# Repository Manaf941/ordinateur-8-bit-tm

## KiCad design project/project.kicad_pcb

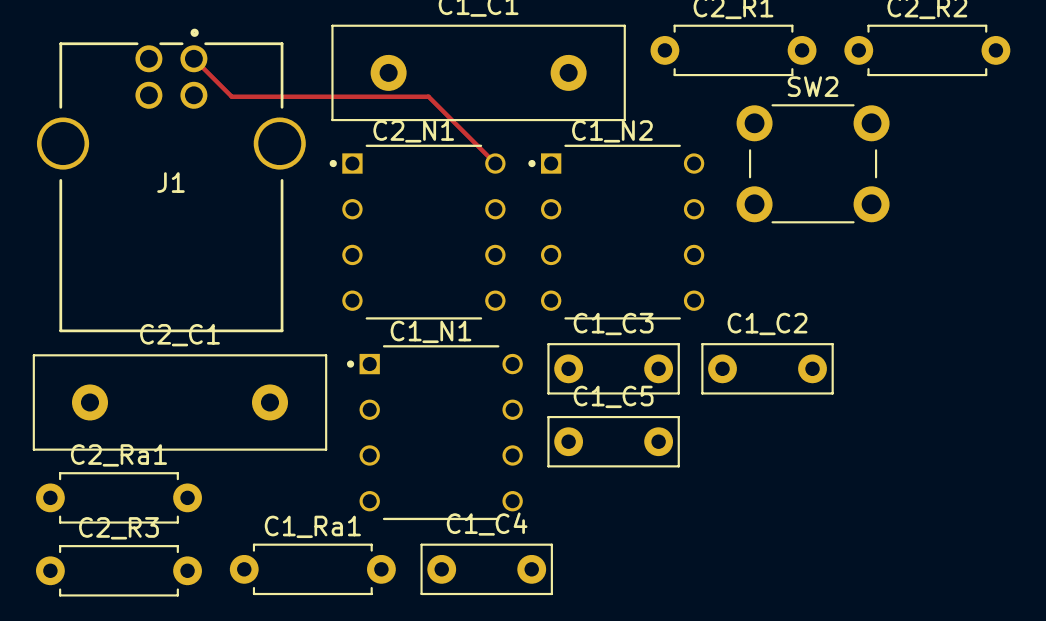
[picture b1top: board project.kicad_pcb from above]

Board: 2 copper layers, 16 parts (0 on the bottom side), 11 nets.

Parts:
C1_C1, C2_C1: 0.1µF; C_Disc_D16.0mm_W5.0mm_P10.00mm
C1_C2, C1_C4, C1_C5: 0.01µF; C_Disc_D7.0mm_W2.5mm_P5.00mm
C1_C3: 0.1µF; C_Disc_D7.0mm_W2.5mm_P5.00mm
C1_N1, C1_N2, C2_N1: NE555P; DIP794W45P254L959H508Q8
C1_Ra1: 100Ω; R_Axial_DIN0207_L6.3mm_D2.5mm_P7.62mm_Horizontal
C2_R1, C2_R2, C2_R3: 1kΩ; R_Axial_DIN0207_L6.3mm_D2.5mm_P7.62mm_Horizontal
C2_Ra1: 1MΩ; R_Axial_DIN0207_L6.3mm_D2.5mm_P7.62mm_Horizontal
J1: 292304-1; CONN4-292304_TEC
SW2: SW_Push_Dual; SW_PUSH_6mm

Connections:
unnamed: C1_C1.1, C1_N1.2 (TRIG), C1_N1.6 (THRES)
unnamed: C1_C1.2, C1_C2.2, C1_C3.2, C1_C4.2, C1_C5.2, C1_N1.1 (GND), C1_N2.1 (GND), C1_N2.6 (THRES), C2_C1.2, C2_N1.1 (GND), J1.4
unnamed: C1_C2.1, C1_N1.5 (CONT)
unnamed: C1_C3.1, C1_N1.8 (VCC), C1_N2.8 (VCC), C1_Ra1.1, C2_N1.8 (VCC), C2_R1.1, C2_R2.1, C2_R3.1, C2_Ra1.1, J1.1
unnamed: C1_C4.1, C1_N2.5 (CONT)
unnamed: C1_C5.1, C2_N1.5 (CONT)
unnamed: C1_N1.7 (DISCH), C1_Ra1.2
unnamed: C1_N2.2 (TRIG), C2_R3.2
unnamed: C1_N2.4 (RESET), C2_R1.2
unnamed: C2_C1.1, C2_N1.6 (THRES), C2_N1.7 (DISCH), C2_Ra1.2
unnamed: C2_N1.2 (TRIG), C2_R2.2

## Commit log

2023-02-02 add .gitignore
2023-02-02 Remove .DS_Store
2023-02-23 + d'instructions
2023-02-23 Table d'instruction
2023-02-23 Petit fix
2023-02-23 JUMPZ fix
2023-02-23 remove duplicate line
2023-03-16 register table, basic assembly compiler
2023-03-16 fix LD+JUMP, add instruction register
2023-03-16 compile.mjs: complete table of instructions
2023-03-30 update proj
2023-05-03 wawa
2023-05-04 Remove project.circ
2023-05-19 new instruction table, ram, remove pc and 5 ticks
2023-10-10 instructions.md => spec.md
2023-10-10 Update repo
2023-10-10 Upload PCB Schema (05.10.23)
2023-10-12 kicad
2023-10-12 move silver-lamp here
2023-11-07 Remove third multiplexer
2023-11-08 clean code a little
2023-11-08 MAX_CODE_SIZE issue
2023-11-08 RAM fix
2023-11-10 modify fibonacci example
2023-11-10 dossier tm logisim-1.jpg
2023-11-10 Dossier TM.pdf
